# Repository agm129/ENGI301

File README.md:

# ENGI301
Repository for ENGI301 course work

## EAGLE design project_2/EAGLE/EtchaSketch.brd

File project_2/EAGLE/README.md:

This folder contains all of the EAGLE files I generated for this project.

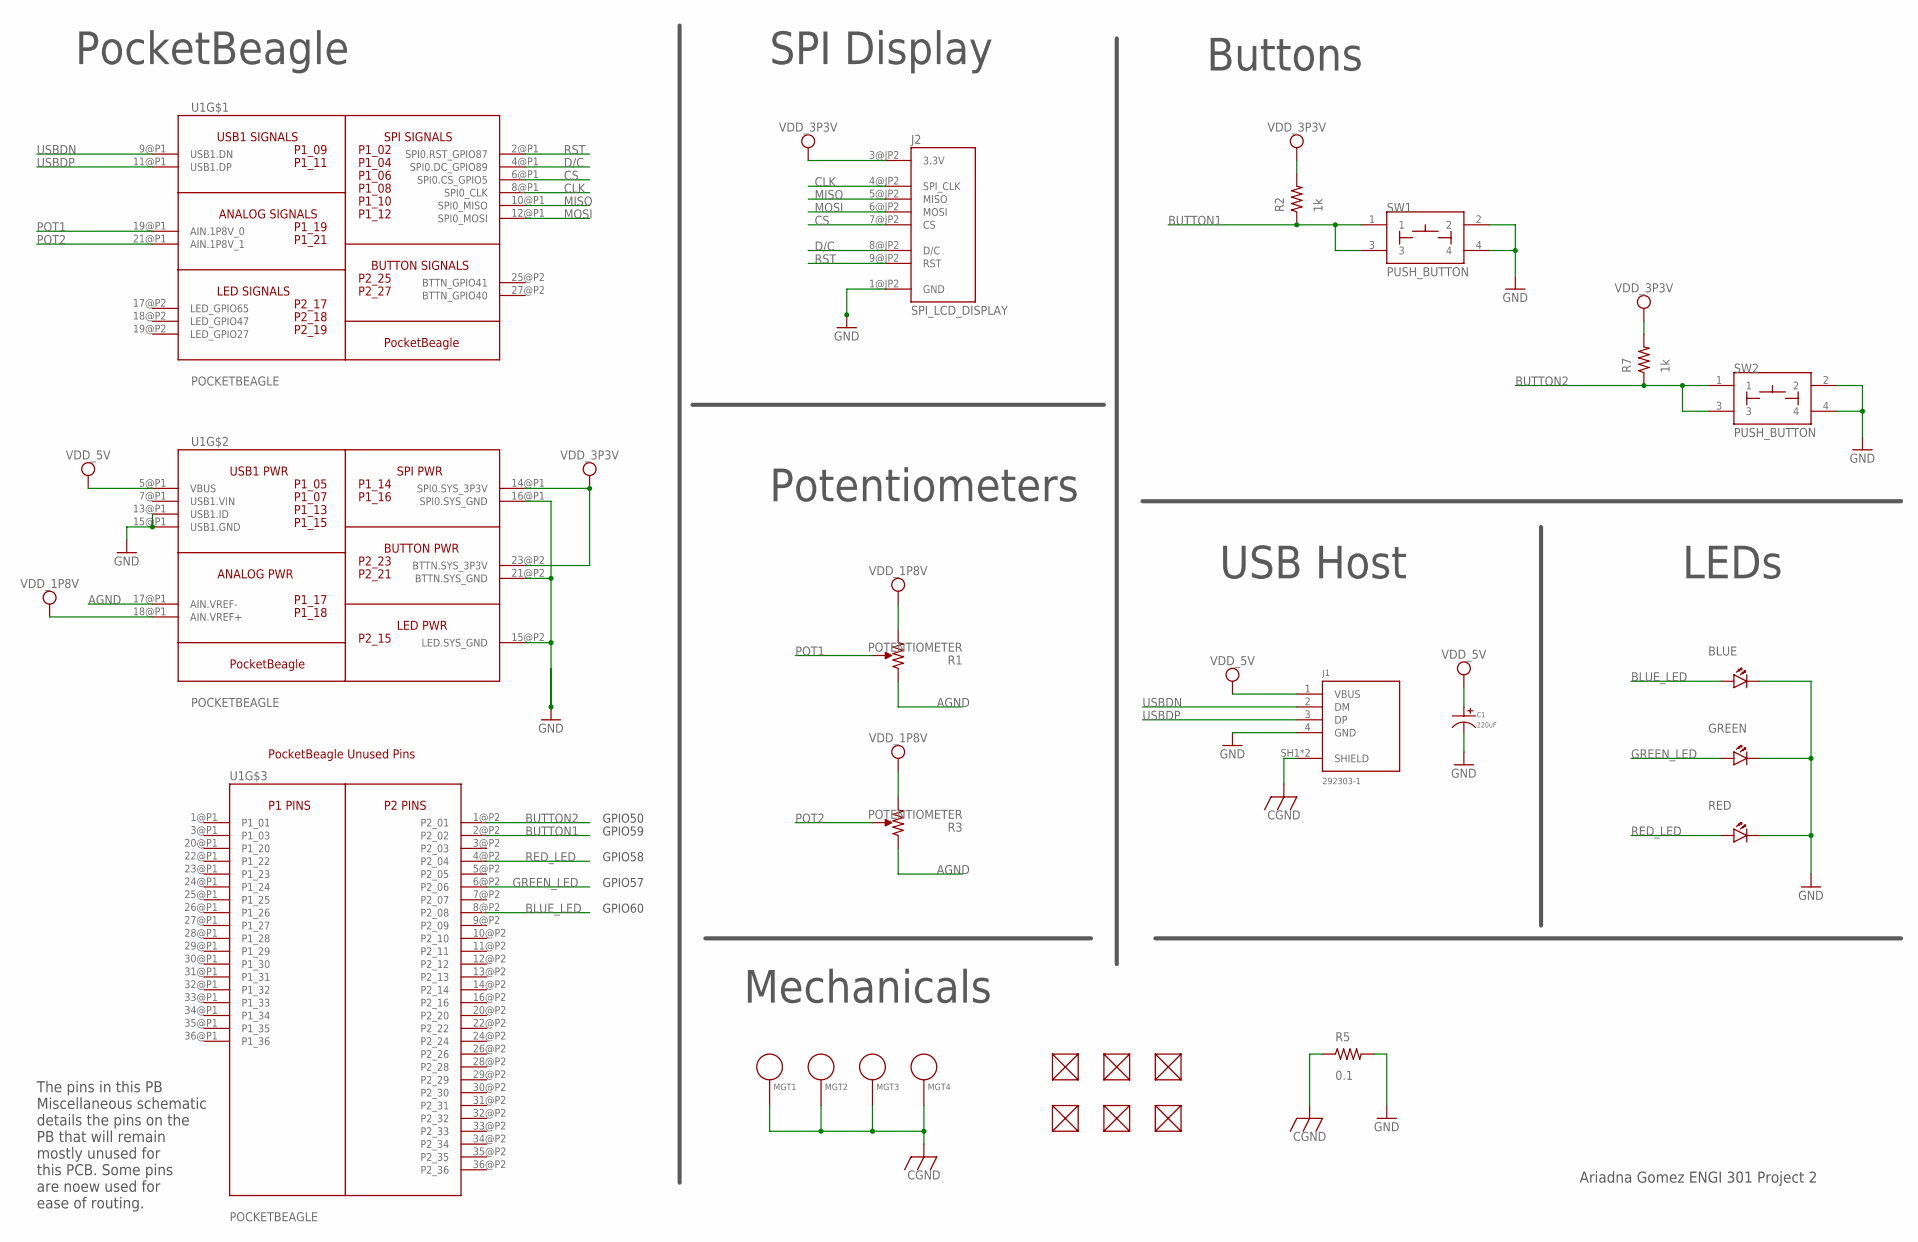
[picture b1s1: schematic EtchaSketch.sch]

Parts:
BLUE: LED; EIA-STD
C1: 220uF; CP10MM
FUD1, FUD2, FUD3, FUD4, FUD5, FUD6: FIDUCIAL; FIDUCIAL_40MIL
GREEN: LED; EIA-STD
J1: 292303-1; TE_292303-1
J2: SPI_LCD_DISPLAY
MGT1, MGT2, MGT3, MGT4: MOUNTING_HOLE
R1, R3: POTENTIOMETER; POT-PO90S
R2, R7: 1k; R0603
R5: 0.1; R0805
RED: LED; EIA-STD
SW1, SW2: PUSH_BUTTON; BUTTON_12.5MM
U1: POCKETBEAGLE

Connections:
AGND: R1.CCW, R3.CCW, U1.17@P1 (AIN.VREF-)
BLUE_LED: BLUE.ANODE, U1.8@P2 (P2_08)
BUTTON1: R2.1, SW1.1, SW1.3, U1.2@P2 (P2_02)
BUTTON2: R7.1, SW2.1, SW2.3, U1.1@P2 (P2_01)
CGND: J1.SH1 (SHIELD), J1.SH2 (SHIELD), MGT1.P$1, MGT2.P$1, MGT3.P$1, MGT4.P$1, R5.1
CLK: J2.4@JP2 (SPI_CLK), U1.8@P1 (SPI0_CLK)
CS: J2.7@JP2 (CS), U1.6@P1 (SPI0.CS_GPIO5)
D/C: J2.8@JP2 (D/C), U1.4@P1 (SPI0.DC_GPIO89)
GND: BLUE.CATHODE, C1.P$2, GREEN.CATHODE, J1.4 (GND), J2.1@JP2 (GND), R5.2, RED.CATHODE, SW1.2, SW1.4, SW2.2, SW2.4, U1.13@P1 (USB1.ID), U1.15@P1 (USB1.GND), U1.15@P2 (LED.SYS_GND), U1.16@P1 (SPI0.SYS_GND), U1.21@P2 (BTTN.SYS_GND)
GREEN_LED: GREEN.ANODE, U1.6@P2 (P2_06)
MISO: J2.5@JP2 (MISO), U1.10@P1 (SPI0_MISO)
MOSI: J2.6@JP2 (MOSI), U1.12@P1 (SPI0_MOSI)
POT1: R1.S, U1.19@P1 (AIN.1P8V_0)
POT2: R3.S, U1.21@P1 (AIN.1P8V_1)
RED_LED: RED.ANODE, U1.4@P2 (P2_04)
RST: J2.9@JP2 (RST), U1.2@P1 (SPI0.RST_GPIO87)
USBDN: J1.2 (DM), U1.9@P1 (USB1.DN)
USBDP: J1.3 (DP), U1.11@P1 (USB1.DP)
VDD_1P8V: R1.CW, R3.CW, U1.18@P1 (AIN.VREF+)
VDD_3P3V: J2.3@JP2 (3.3V), R2.2, R7.2, U1.14@P1 (SPI0.SYS_3P3V), U1.23@P2 (BTTN.SYS_3P3V)
VDD_5V: C1.P$1, J1.1 (VBUS), U1.5@P1 (VBUS)

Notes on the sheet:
Ariadna Gomez ENGI 301 Project 2
PocketBeagle
SPI Display
Potentiometers
USB Host
LEDs
Buttons
The pins in this PB Miscellaneous schematic details the pins on the PB that will remain mostly unused for this PCB. Some pins are noew used for ease of routing.
Mechanicals
GPIO50
GPIO59
GPIO58
GPIO57
GPIO60

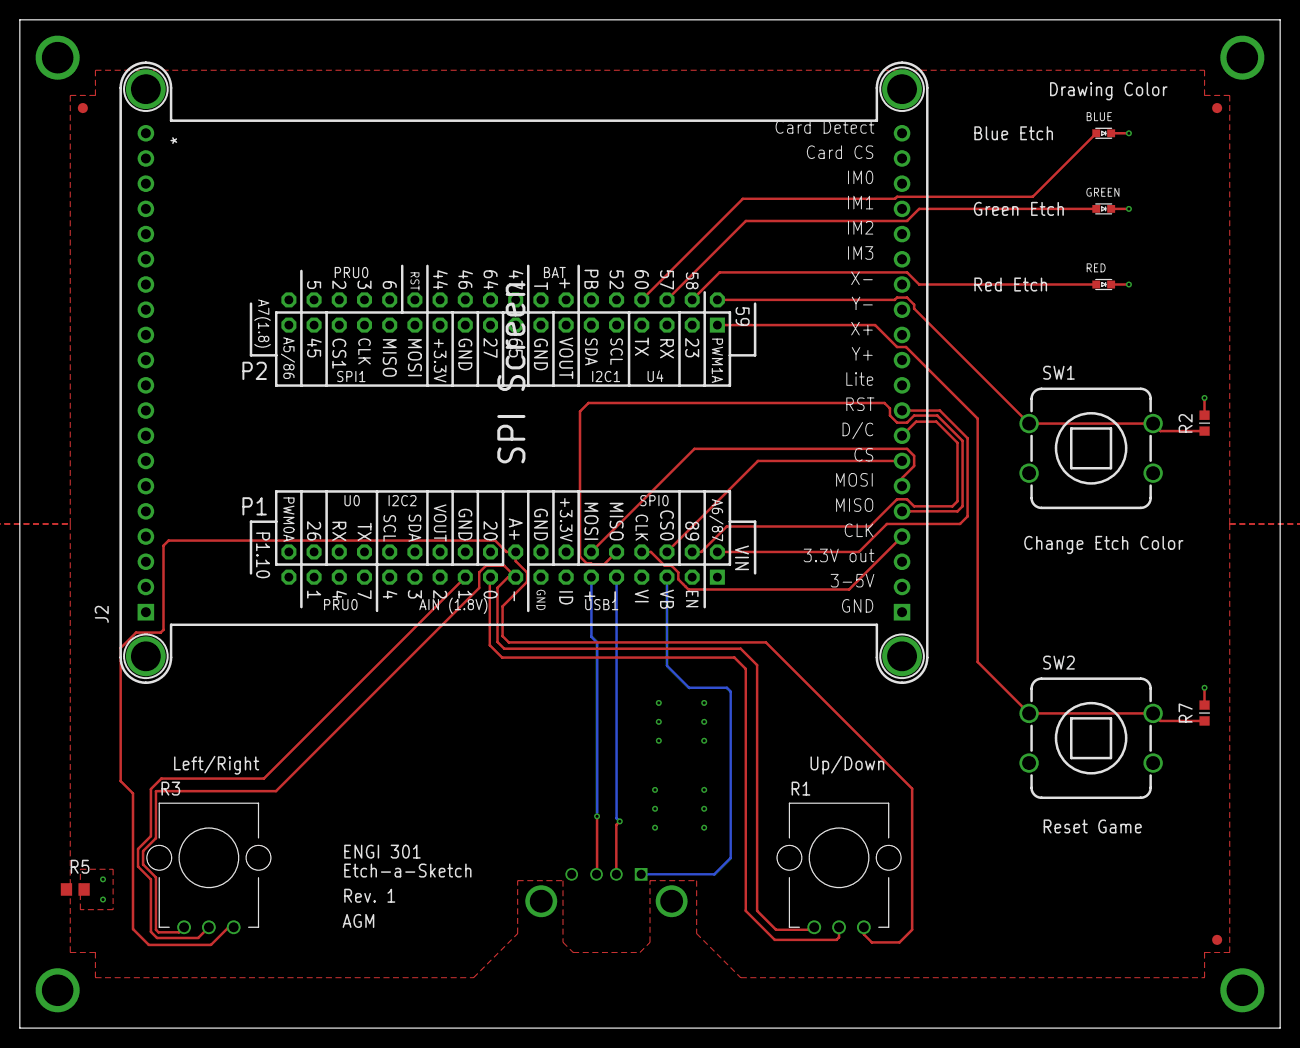
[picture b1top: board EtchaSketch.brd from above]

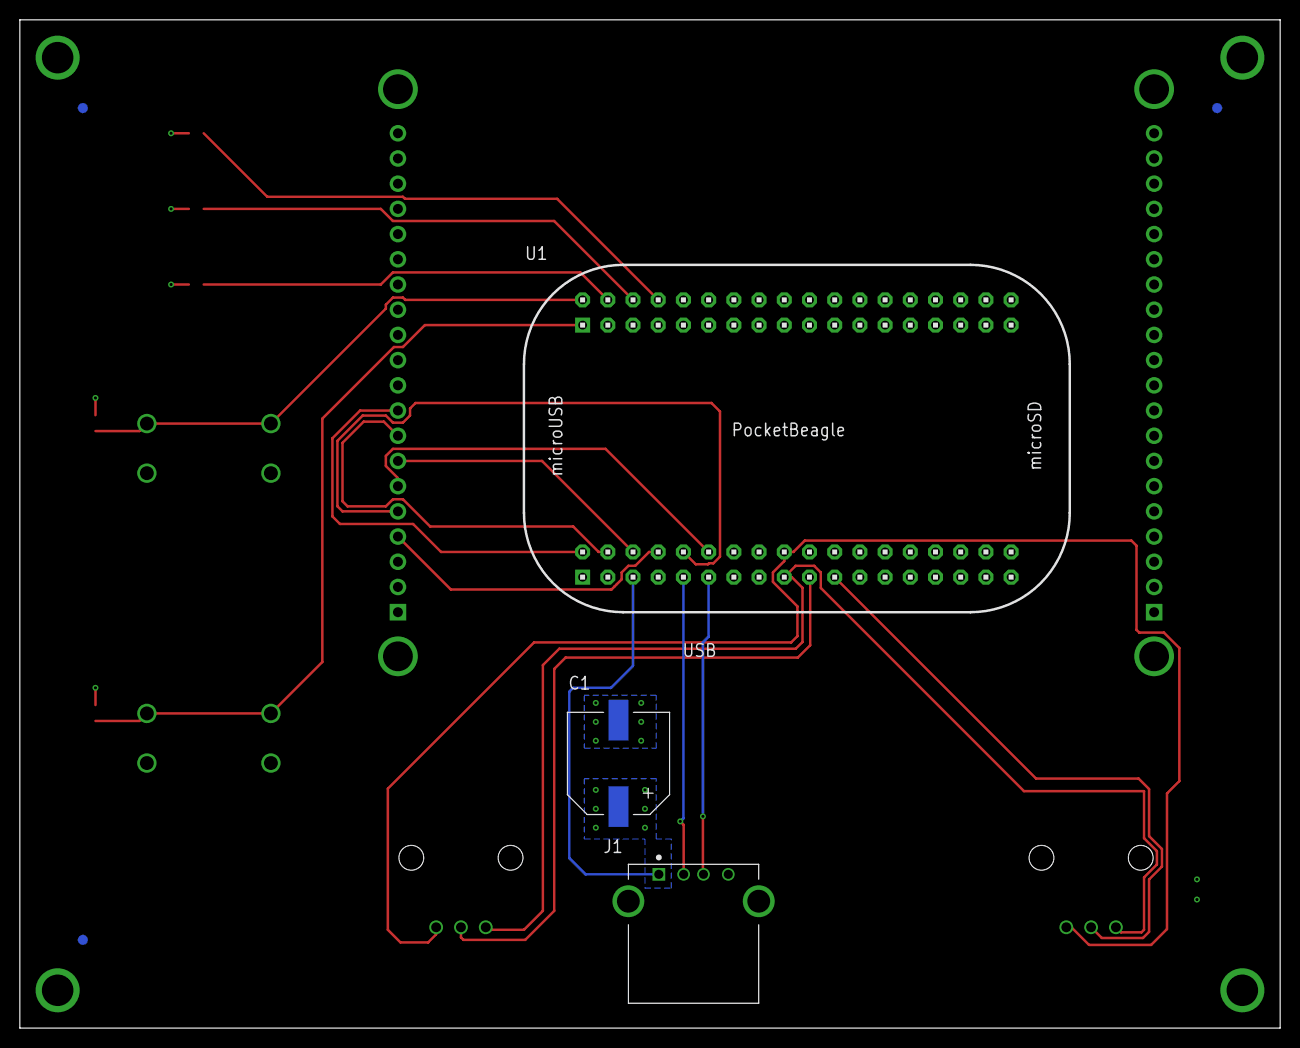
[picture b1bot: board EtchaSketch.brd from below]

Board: 4 copper layers, 127.0 x 101.6 mm, 24 parts (6 on the bottom side), 21 nets.

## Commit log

2022-09-25 Committing Simple Calc File Done in Class
2022-09-26 Uploading blink_led
2022-09-26 uploading final simple_calc file
2022-09-26 upload final simple_calc_class version
2022-09-26 added python2 compatibility
2022-09-26 added documentation
2022-10-08 Add project description via file upload
2022-10-08 Create project_1 folder
2022-10-08 Create project_1/docs folder
2022-10-08 Create project_description
2022-10-08 Add project proposal slides
2022-12-05 File for mechanical block diagram submission
2022-12-05 Create docs
2022-12-05 Uploaded mechanical block diagram
2022-12-16 Uploaded project EAGLE files
2022-12-16 MFG file upload
2022-12-16 BOM and Schematic file upload
2022-12-16 Update project_description
2022-12-16 Project Code Upload
